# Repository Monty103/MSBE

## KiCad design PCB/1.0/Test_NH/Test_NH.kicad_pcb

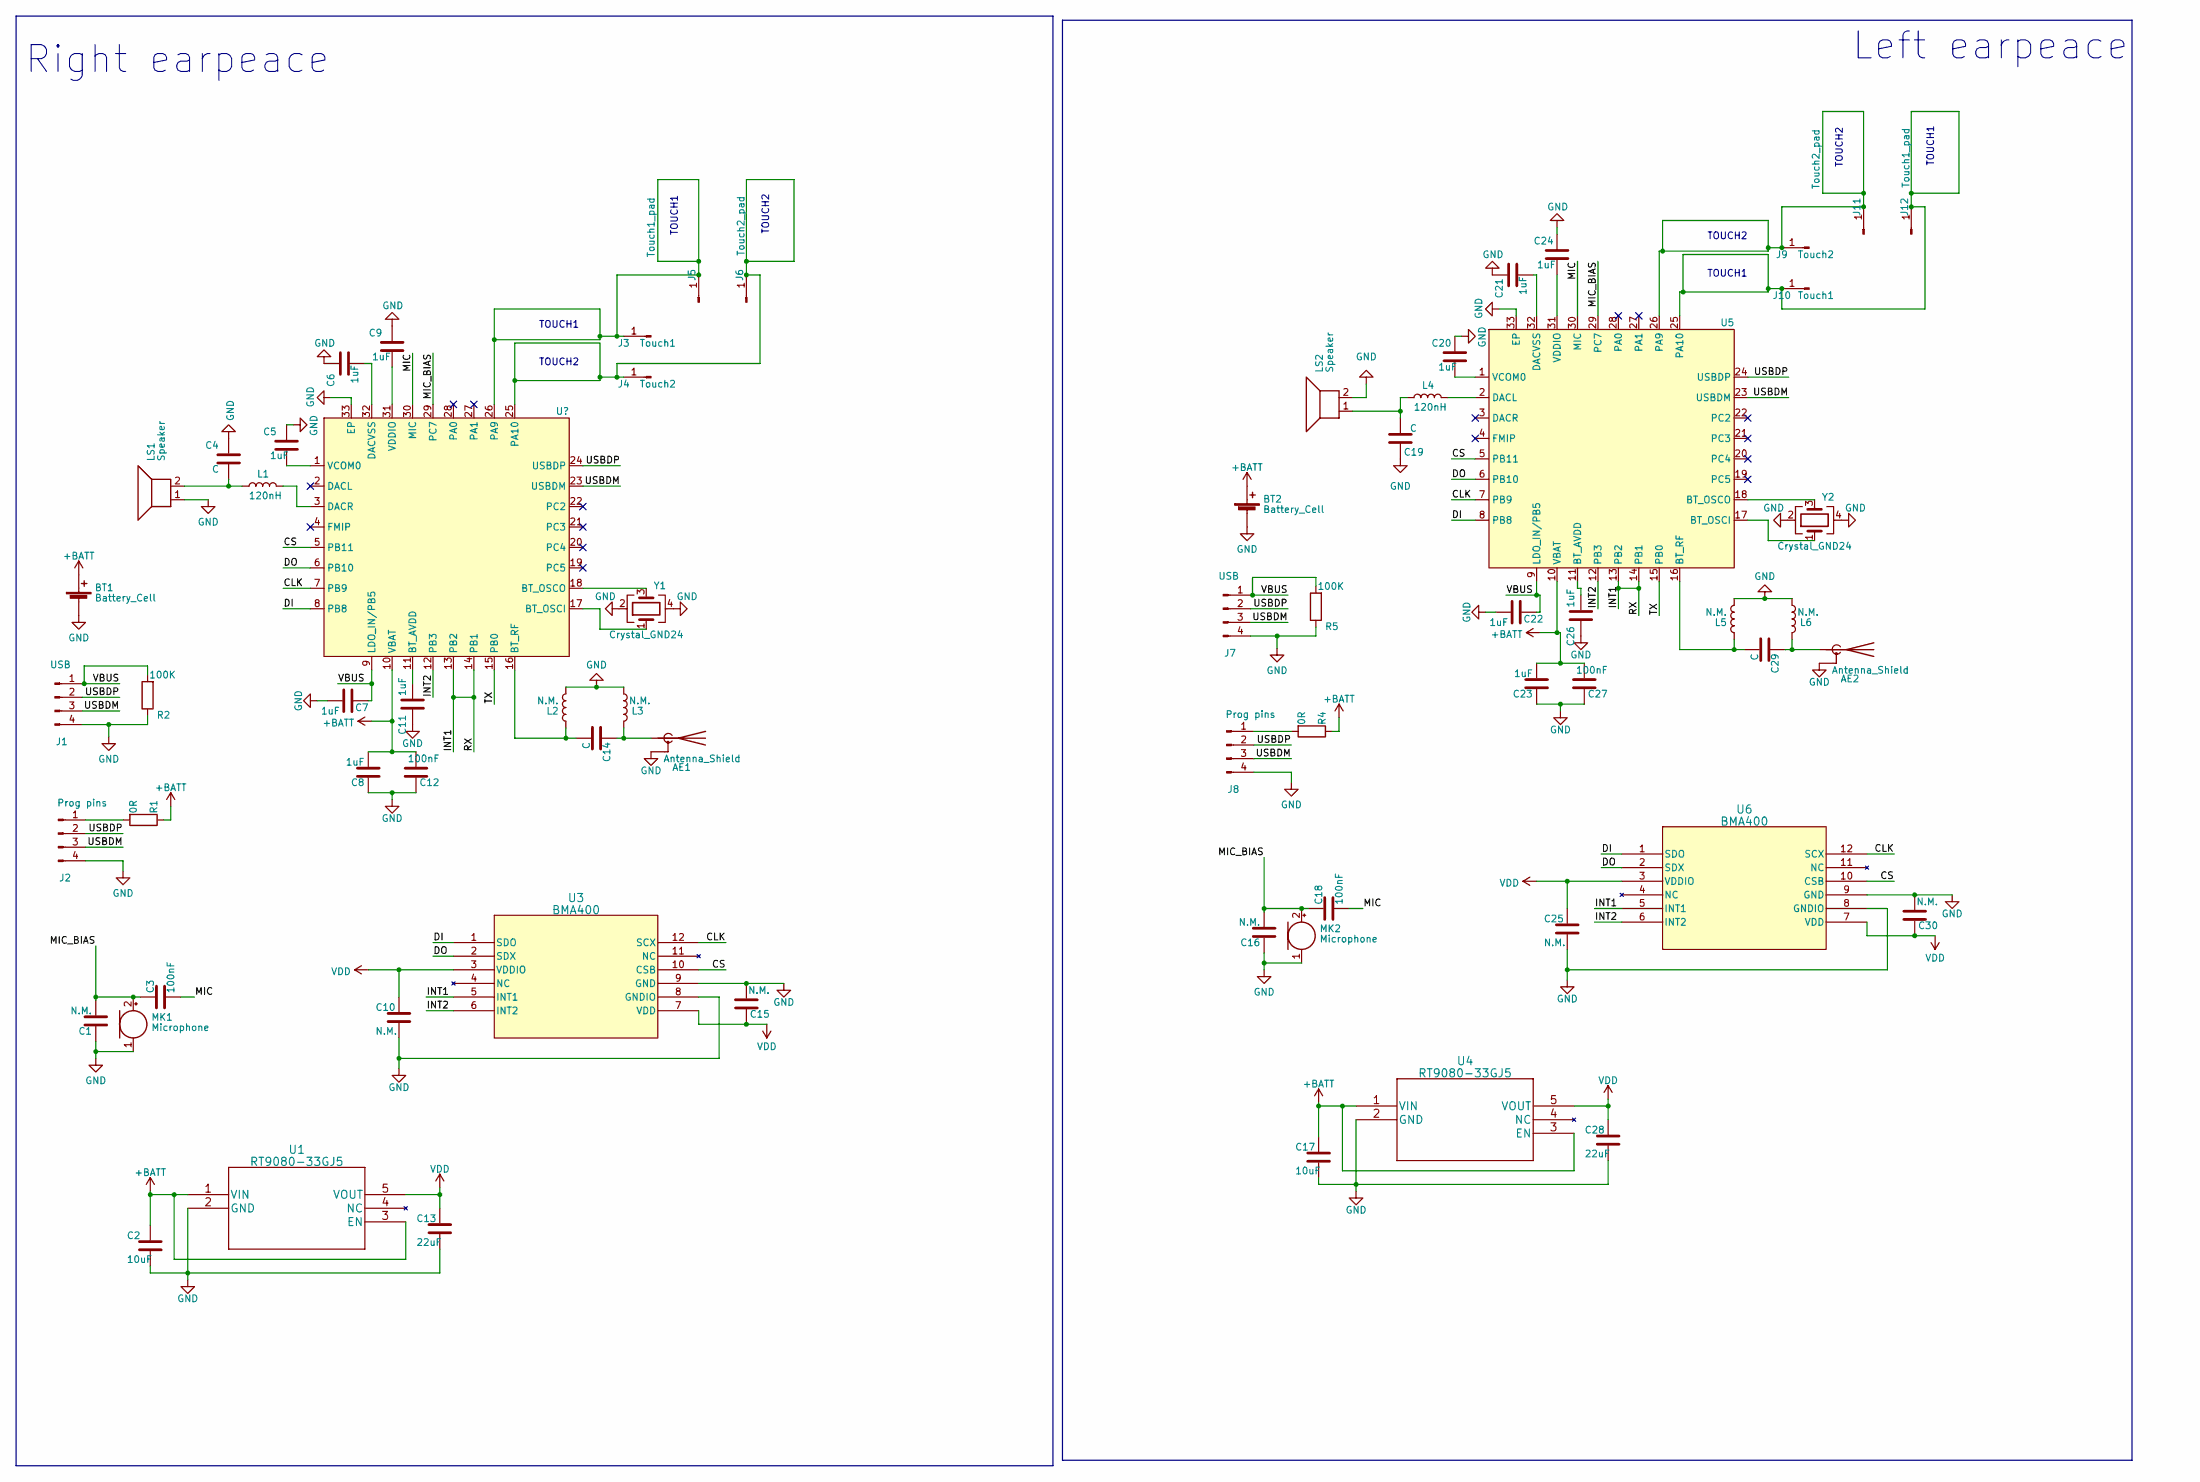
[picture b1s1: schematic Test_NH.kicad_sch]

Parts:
AE1, AE2: Antenna_Shield; Texas_SWRA117D_2.4GHz_Left
BT1, BT2: Battery_Cell; Pad_2Pin_1.5x0.8mm
C1, C10, C15, C16, C25, C30: N.M.; C_0201_0603Metric_Pad0.64x0.40mm_HandSolder
C2, C17: 10uF; C_0201_0603Metric_Pad0.64x0.40mm_HandSolder
C3, C12, C18, C27: 100nF; C_0201_0603Metric_Pad0.64x0.40mm_HandSolder
C4, C14, C19, C29: C; C_0201_0603Metric_Pad0.64x0.40mm_HandSolder
C5, C6, C7, C8, C9, C11, C20, C21, C22, C23, C24, C26: 1uF; C_0201_0603Metric_Pad0.64x0.40mm_HandSolder
C13, C28: 22uF; C_0201_0603Metric_Pad0.64x0.40mm_HandSolder
J1, J7: USB; Pad_4Pin_1.5x0.8mm
J2, J8: Prog pins; Pad_4Pin_1.5x0.8mm
J3, J10: Touch1; Pad_2Pin_1.5x0.8mm
J4, J9: Touch2; Pad_2Pin_1.5x0.8mm
J5, J12: Touch1_pad; Pad_2Pin_1.5x0.8mm
J6, J11: Touch2_pad; Pad_2Pin_1.5x0.8mm
L1, L4: 120nH; L_0402_1005Metric_Pad0.77x0.64mm_HandSolder
L2, L3, L5, L6: N.M.; L_0402_1005Metric_Pad0.77x0.64mm_HandSolder
LS1, LS2: Speaker; Pad_2Pin_1.5x0.8mm
MK1, MK2: Microphone; Pad_2Pin_1.5x0.8mm
R1, R4: 0R; R_0201_0603Metric_Pad0.64x0.40mm_HandSolder
R2, R5: 100K; R_0201_0603Metric_Pad0.64x0.40mm_HandSolder
U1, U4: RT9080-33GJ5; RT9080
U2, U5: QFN-32-1EP_4x4mm_P0.4mm_EP2.65x2.65mm
U3, U6: BMA400; QFN_BMA400_BOS
Y1, Y2: Crystal_GND24; Crystal_24MHz-ECS-240-12-37B-CKY-TR

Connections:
+BATT: BT1.1 (+), BT2.1 (+), C2.1, C8.2, C12.2, C17.1, C23.2, C27.2, R1.1, R4.1, U1.1 (VIN), U1.3 (EN), U2.10 (VBAT), U4.1 (VIN), U4.3 (EN), U5.10 (VBAT)
/CLK: U2.7 (PB9), U3.12 (SCX), U5.7 (PB9), U6.12 (SCX)
/CS: U2.5 (PB11), U3.10 (CSB), U5.5 (PB11), U6.10 (CSB)
/DI: U2.8 (PB8), U3.1 (SDO), U5.8 (PB8), U6.1 (SDO)
/DO: U2.6 (PB10), U3.2 (SDX), U5.6 (PB10), U6.2 (SDX)
/INT1: U2.13 (PB2), U2.14 (PB1), U3.5 (INT1), U5.13 (PB2), U5.14 (PB1), U6.5 (INT1); also elsewhere on the board
/INT2: U2.12 (PB3), U3.6 (INT2), U5.12 (PB3), U6.6 (INT2)
/MIC: C3.2, C18.2, U2.30 (MIC), U5.30 (MIC)
/MIC_BIAS: C1.2, C3.1, C16.2, C18.1, MK1.2 (+), MK2.2 (+), U2.29 (PC7), U5.29 (PC7)
/TX: U2.15 (PB0), U5.15 (PB0); also elsewhere on the board
/USBDM: J1.3, J2.3, J7.3, J8.3, U2.23 (USBDM), U5.23 (USBDM)
/USBDP: J1.2, J2.2, J7.2, J8.2, U2.24 (USBDP), U5.24 (USBDP)
/VBUS: C7.1, C22.1, J1.1, J7.1, R2.2, R5.2, U2.9 (LDO_IN/PB5), U5.9 (LDO_IN/PB5)
GND: AE1.2 (Shield), AE2.2 (Shield), BT1.2 (-), BT2.2 (-), C1.1, C2.2, C4.1, C5.1, C6.1, C7.2, C8.1, C9.1, C10.2, C11.1, C12.1, C13.2, C15.2, C16.1, C17.2, C19.1, C20.1, C21.1, C22.2, C23.1, C24.1, C25.2, C26.1, C27.1, C28.2, C30.2, J1.4, J2.4, J7.4, J8.4, L2.2, L3.1, L5.2, L6.1, LS1.1, LS2.2, MK1.1 (-), MK2.1 (-), R2.1, R5.1, U1.2 (GND), U2.33 (EP), U3.8 (GNDIO), U3.9 (GND), U4.2 (GND), U5.33 (EP), U6.8 (GNDIO), U6.9 (GND), Y1.2, Y1.4, Y2.2, Y2.4
unnamed: AE1.1 (A), C14.1, L3.2
unnamed: AE2.1 (A), C29.1, L6.2
unnamed: C4.2, L1.1, LS1.2
unnamed: C19.2, L4.1, LS2.1
unnamed: J2.1, R1.2
unnamed: J3.1, J5.1, U2.26 (PA9)
unnamed: J4.1, J6.1, U2.25 (PA10)
unnamed: J8.1, R4.2
unnamed: J10.1, J12.1, U5.25 (PA10)
unnamed: J9.1, J11.1, U5.26 (PA9)
unnamed: C11.2, U2.11 (BT_AVDD)
unnamed: U2.17 (BT_OSCI), Y1.1
unnamed: U2.18 (BT_OSCO), Y1.3
unnamed: C14.2, L2.1, U2.16 (BT_RF)
unnamed: L1.2, U2.3 (DACR)
unnamed: C6.2, U2.32 (DACVSS)
unnamed: C5.2, U2.1 (VCOM0)
unnamed: C9.2, U2.31 (VDDIO)
unnamed: C26.2, U5.11 (BT_AVDD)
unnamed: U5.17 (BT_OSCI), Y2.1
unnamed: U5.18 (BT_OSCO), Y2.3
unnamed: C29.2, L5.1, U5.16 (BT_RF)
unnamed: L4.2, U5.2 (DACL)
unnamed: C21.2, U5.32 (DACVSS)
unnamed: C20.2, U5.1 (VCOM0)
unnamed: C24.2, U5.31 (VDDIO)
VDD: C10.1, C13.1, C15.1, C25.1, C28.1, C30.1, U1.5 (VOUT), U3.3 (VDDIO), U3.7 (VDD), U4.5 (VOUT), U6.3 (VDDIO), U6.7 (VDD)

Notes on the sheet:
TOUCH1
TOUCH2
Right earpeace
Left earpeace

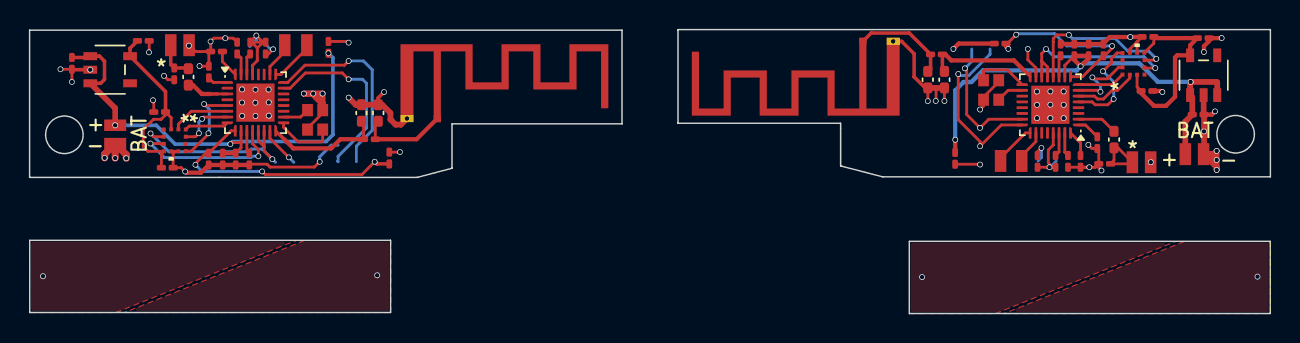
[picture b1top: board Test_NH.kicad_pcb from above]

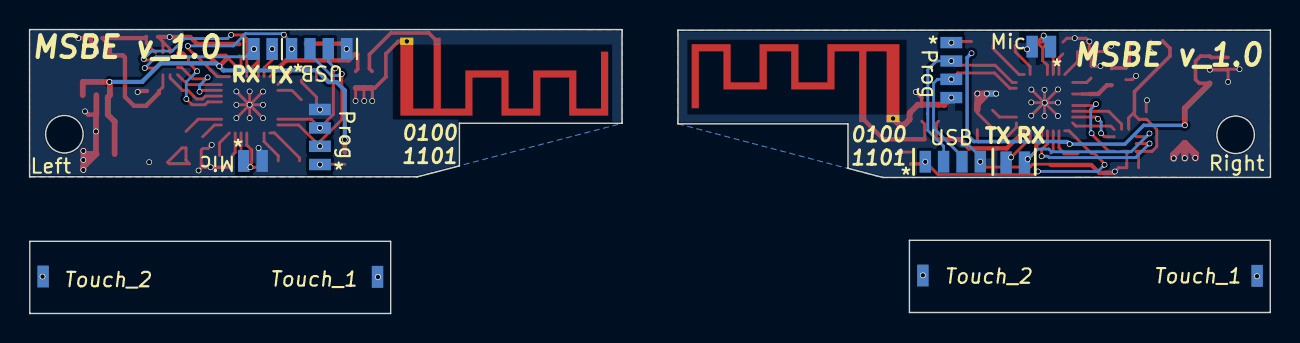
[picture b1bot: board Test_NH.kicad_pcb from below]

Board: 2 copper layers, 86.0 x 19.7 mm, 70 parts (12 on the bottom side), 41 nets.

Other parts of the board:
LS1#2, LS1#3: Speaker; Pad_2Pin_1.5x0.8mm

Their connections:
/INT1: LS1#2.2, LS1#3.2; also elsewhere on the board
/TX: LS1#2.1, LS1#3.1; also elsewhere on the board

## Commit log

2024-12-17 update files
2025-02-07 Updated files
2025-04-25 New MCU update
